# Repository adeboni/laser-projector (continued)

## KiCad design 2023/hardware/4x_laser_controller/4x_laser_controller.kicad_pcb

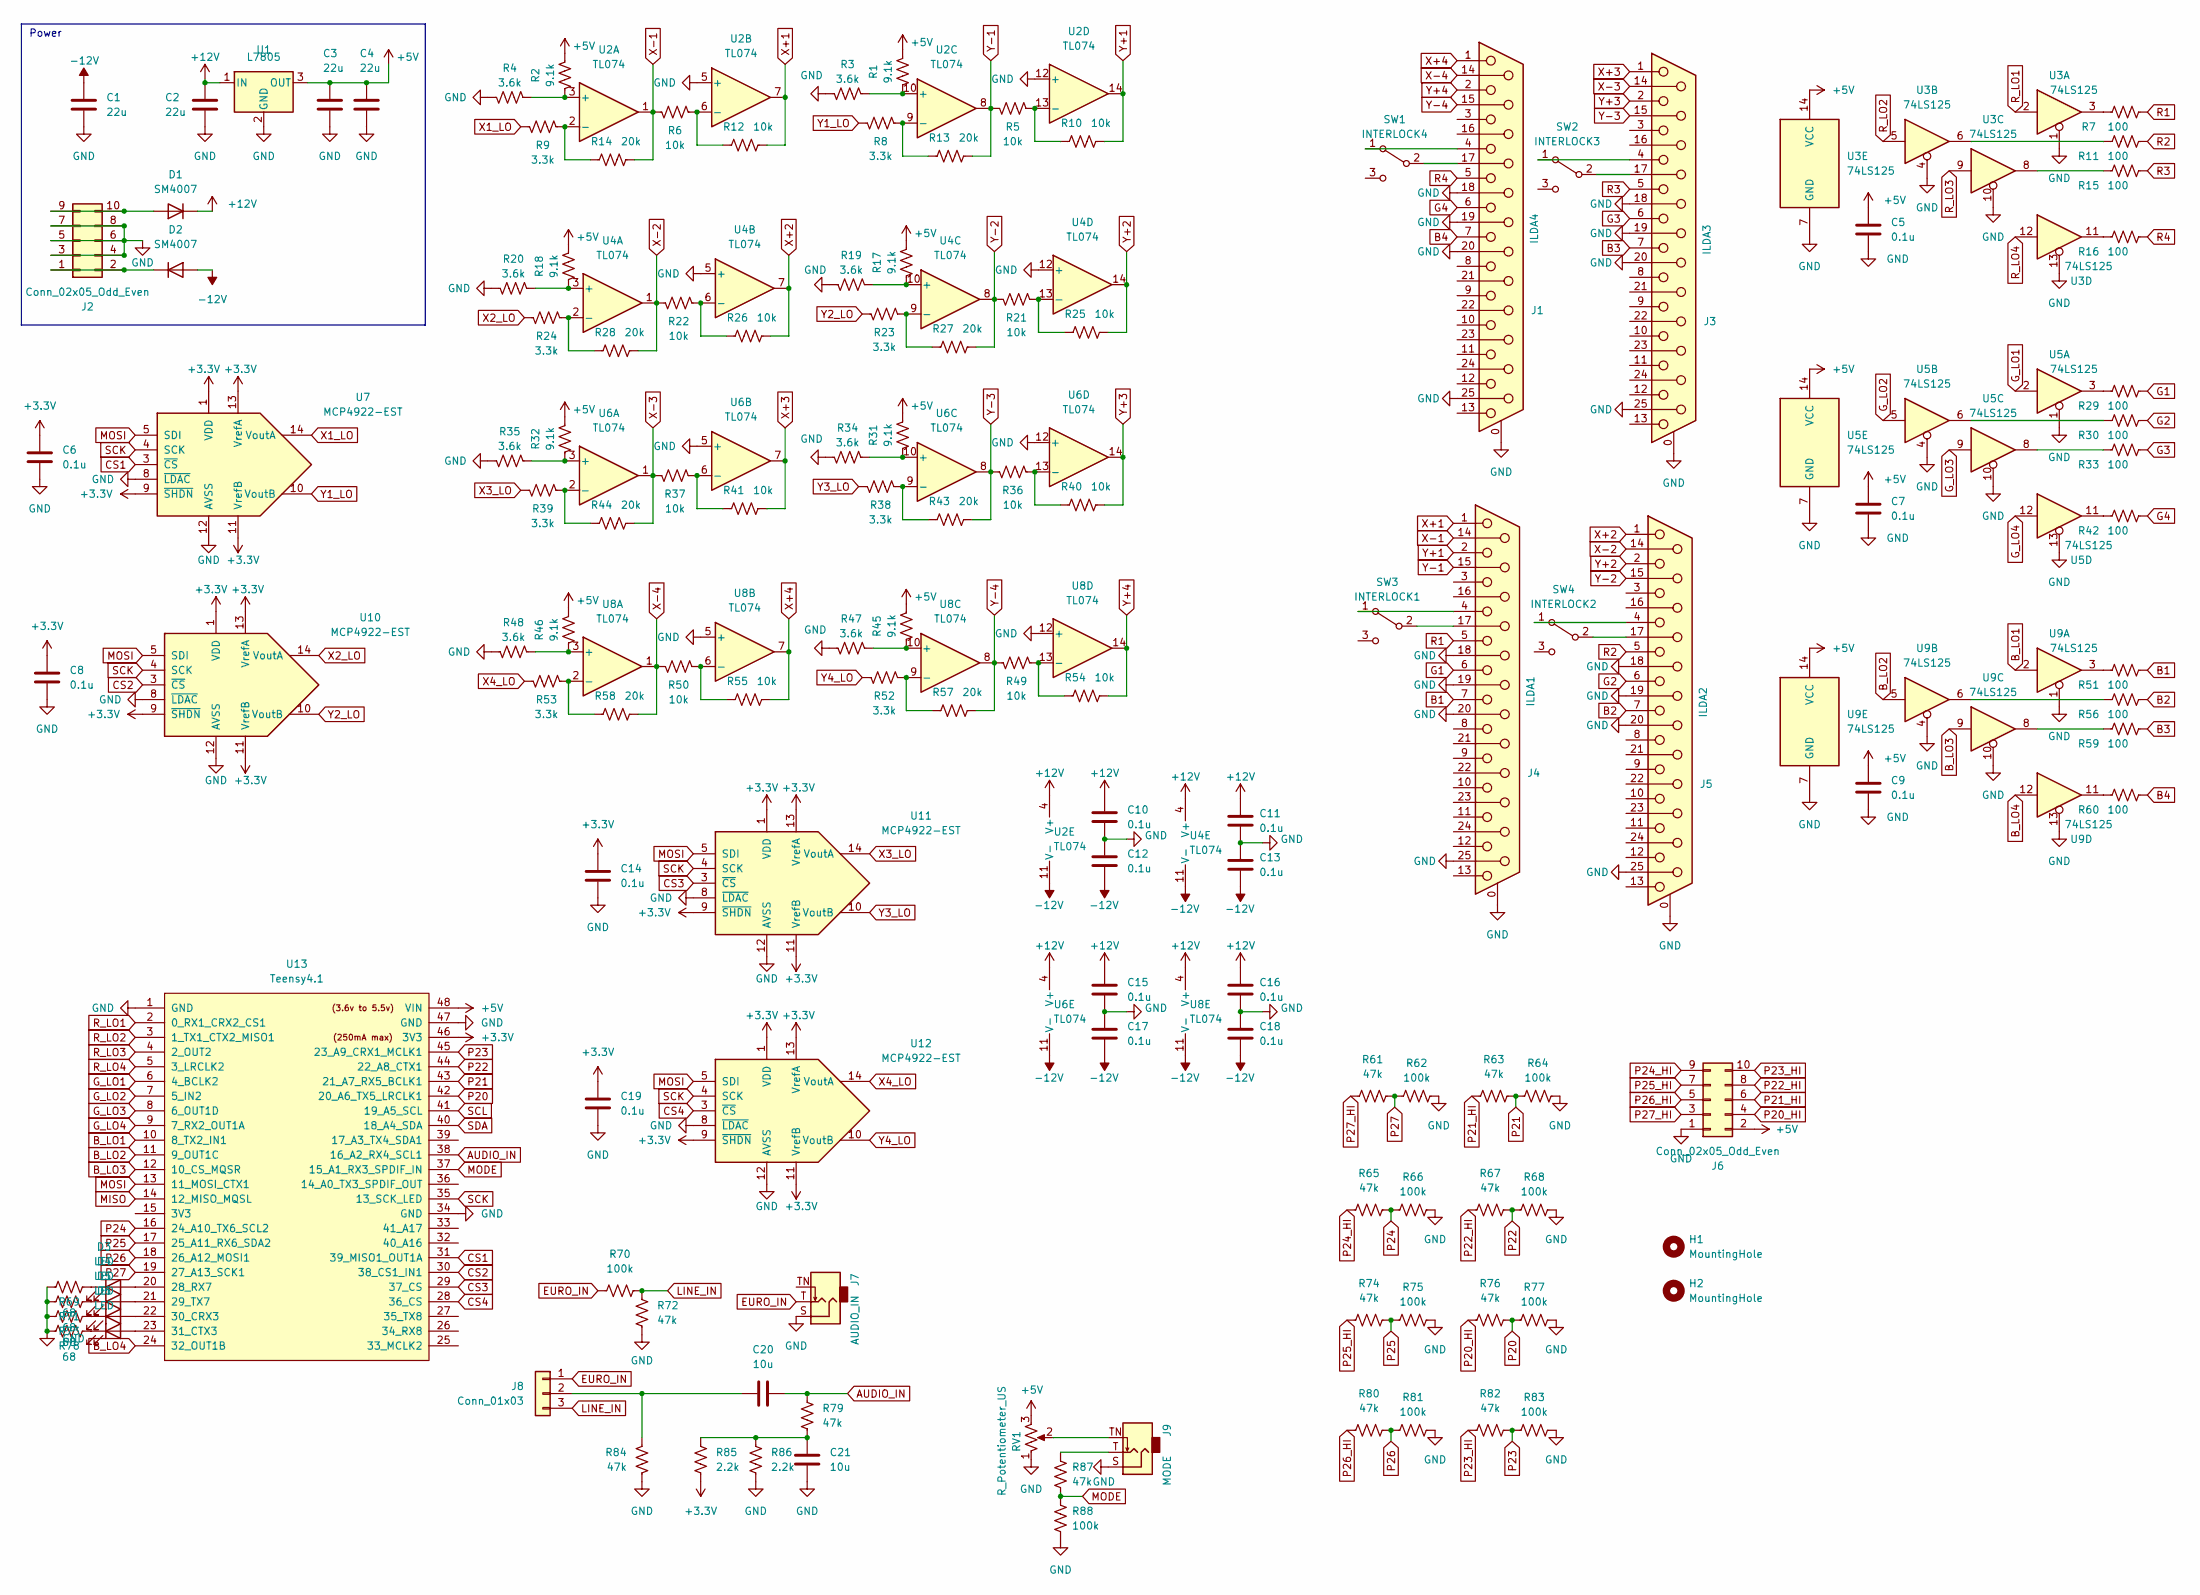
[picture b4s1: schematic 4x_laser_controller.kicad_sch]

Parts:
C1, C2, C3, C4: 22u; C_0805_2012Metric
C5, C6, C7, C8, C9, C10, C11, C12, C13, C14, C15, C16, C17, C18, C19: 0.1u; C_0603_1608Metric
C20, C21: 10u; C_0603_1608Metric
D1, D2: SM4007; D_SOD-123
D3, D4, D5, D6: LED; LED_D3.0mm
H1, H2: MountingHole; MountingHole_2.2mm_M2
J1: ILDA4; DSUB-25_Female_Vertical_P2.77x2.84mm_MountingHoles
J2, J6: Conn_02x05_Odd_Even; IDC-Header_2x05_P2.54mm_Vertical
J3: ILDA3; DSUB-25_Female_Vertical_P2.77x2.84mm_MountingHoles
J4: ILDA1; DSUB-25_Female_Vertical_P2.77x2.84mm_MountingHoles
J5: ILDA2; DSUB-25_Female_Vertical_P2.77x2.84mm_MountingHoles
J7: AUDIO_IN; Jack_3.5mm_QingPu_WQP-PJ398SM_Vertical_CircularHoles
J8: Conn_01x03; PinHeader_1x03_P2.54mm_Vertical
J9: MODE; Jack_3.5mm_QingPu_WQP-PJ398SM_Vertical_CircularHoles
R1, R2, R17, R18, R31, R32, R45, R46: 9.1k; R_0603_1608Metric
R3, R4, R19, R20, R34, R35, R47, R48: 3.6k; R_0603_1608Metric
R5, R6, R10, R12, R21, R22, R25, R26, R36, R37, R40, R41, R49, R50, R54, R55: 10k; R_0603_1608Metric
R7, R11, R15, R16, R29, R30, R33, R42, R51, R56, R59, R60: 100; R_0603_1608Metric
R8, R9, R23, R24, R38, R39, R52, R53: 3.3k; R_0603_1608Metric
R13, R14, R27, R28, R43, R44, R57, R58: 20k; R_0603_1608Metric
R61, R63, R65, R67, R72, R74, R76, R79, R80, R82, R84, R87: 47k; R_0603_1608Metric
R62, R64, R66, R68, R70, R75, R77, R81, R83, R88: 100k; R_0603_1608Metric
R69, R71, R73, R78: 68; R_0603_1608Metric
R85, R86: 2.2k; R_0603_1608Metric
RV1: R_Potentiometer_US; Potentiometer_Alpha_RD901F-40-00D_Single_Vertical
SW1: INTERLOCK4; Switch_Toggle_SPDT_Mini_SolderLug
SW2: INTERLOCK3; Switch_Toggle_SPDT_Mini_SolderLug
SW3: INTERLOCK1; Switch_Toggle_SPDT_Mini_SolderLug
SW4: INTERLOCK2; Switch_Toggle_SPDT_Mini_SolderLug
U1: L7805; TO-252-2
U2, U4, U6, U8: TL074; SOIC-14_3.9x8.7mm_P1.27mm
U3, U5, U9: 74LS125; SOIC-14_3.9x8.7mm_P1.27mm
U7, U10, U11, U12: MCP4922-EST; TSSOP-14_4.4x5mm_P0.65mm
U13: Teensy4.1; Teensy41

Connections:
+3V3: C6.2, C8.2, C14.2, C19.2, R85.1, U7.1 (VDD), U7.9 (~SHDN), U7.11 (VrefB), U7.13 (VrefA), U10.1 (VDD), U10.9 (~SHDN), U10.11 (VrefB), U10.13 (VrefA), U11.1 (VDD), U11.9 (~SHDN), U11.11 (VrefB), U11.13 (VrefA), U12.1 (VDD), U12.9 (~SHDN), U12.11 (VrefB), U12.13 (VrefA), U13.46 (3V3)
+5V: C3.1, C4.1, C5.1, C7.1, C9.1, J6.2, R1.2, R2.2, R17.2, R18.2, R31.2, R32.2, R45.2, R46.2, RV1.3, U1.3 (OUT), U3.14 (VCC), U5.14 (VCC), U9.14 (VCC), U13.48 (VIN)
+12V: C2.1, C10.1, C11.1, C15.1, C16.1, D1.1 (K), U1.1 (IN), U2.4 (V+), U4.4 (V+), U6.4 (V+), U8.4 (V+)
-12V: C1.1, C12.2, C13.2, C17.2, C18.2, D2.2 (A), U2.11 (V-), U4.11 (V-), U6.11 (V-), U8.11 (V-)
AUDIO_IN: C20.2, R79.2, U13.38 (16_A2_RX4_SCL1)
B1: J4.7, R51.2
B2: J5.7, R56.2
B3: J3.7, R59.2
B4: J1.7, R60.2
B_LO1: U9.2, U13.10 (8_TX2_IN1)
B_LO2: U9.5, U13.11 (9_OUT1C)
B_LO3: U9.9, U13.12 (10_CS_MQSR)
B_LO4: U9.12, U13.24 (32_OUT1B)
CS1: U7.3 (~CS), U13.31 (39_MISO1_OUT1A)
CS2: U10.3 (~CS), U13.30 (38_CS1_IN1)
CS3: U11.3 (~CS), U13.29 (37_CS)
CS4: U12.3 (~CS), U13.28 (36_CS)
EURO_IN: J7.T, J8.1, R70.1
G1: J4.6, R29.2
G2: J5.6, R30.2
G3: J3.6, R33.2
G4: J1.6, R42.2
GND: C1.2, C2.2, C3.2, C4.2, C5.2, C6.1, C7.2, C8.1, C9.2, C10.2, C11.2, C12.1, C13.1, C14.1, C15.2, C16.2, C17.1, C18.1, C19.1, C21.1, J1.0 (PAD), J1.18, J1.19, J1.20, J1.25, J2.3, J2.4, J2.5, J2.6, J2.7, J2.8, J3.0 (PAD), J3.18, J3.19, J3.20, J3.25, J4.0 (PAD), J4.18, J4.19, J4.20, J4.25, J5.0 (PAD), J5.18, J5.19, J5.20, J5.25, J6.1, J7.S, J9.S, R3.1, R4.1, R19.1, R20.1, R34.1, R35.1, R47.1, R48.1, R62.1, R64.1, R66.1, R68.1, R69.1, R71.1, R72.1, R73.1, R75.1, R77.1, R78.1, R81.1, R83.1, R84.1, R86.1, R88.2, RV1.1, U1.2 (GND), U2.5 (+), U2.12 (+), U3.1, U3.4, U3.7 (GND), U3.10, U3.13, U4.5 (+), U4.12 (+), U5.1, U5.4, U5.7 (GND), U5.10, U5.13, U6.5 (+), U6.12 (+), U7.8 (~LDAC), U7.12 (AVSS), U8.5 (+), U8.12 (+), U9.1, U9.4, U9.7 (GND), U9.10, U9.13, U10.8 (~LDAC), U10.12 (AVSS), U11.8 (~LDAC), U11.12 (AVSS), U12.8 (~LDAC), U12.12 (AVSS), U13.1 (GND), U13.34 (GND), U13.47 (GND)
G_LO1: U5.2, U13.6 (4_BCLK2)
G_LO2: U5.5, U13.7 (5_IN2)
G_LO3: U5.9, U13.8 (6_OUT1D)
G_LO4: U5.12, U13.9 (7_RX2_OUT1A)
LINE_IN: J8.3, R70.2, R72.2
MISO: U13.14 (12_MISO_MQSL)
MODE: R87.1, R88.1, U13.37 (15_A1_RX3_SPDIF_IN)
MOSI: U7.5 (SDI), U10.5 (SDI), U11.5 (SDI), U12.5 (SDI), U13.13 (11_MOSI_CTX1)
unnamed: C20.1, J8.2, R84.2
unnamed: C21.2, R79.1, R85.2, R86.2
unnamed: D1.2 (A), J2.9, J2.10
unnamed: D2.1 (K), J2.1, J2.2
unnamed: D3.1 (K), R69.2
unnamed: D3.2 (A), U13.20 (28_RX7)
unnamed: D4.1 (K), R71.2
unnamed: D4.2 (A), U13.21 (29_TX7)
unnamed: D5.1 (K), R73.2
unnamed: D5.2 (A), U13.22 (30_CRX3)
unnamed: D6.1 (K), R78.2
unnamed: D6.2 (A), U13.23 (31_CTX3)
unnamed: J1.4, SW1.1 (A)
unnamed: J1.17, SW1.2 (B)
unnamed: J3.4, SW2.1 (A)
unnamed: J3.17, SW2.2 (B)
unnamed: J4.4, SW3.1 (A)
unnamed: J4.17, SW3.2 (B)
unnamed: J5.4, SW4.1 (A)
unnamed: J5.17, SW4.2 (B)
unnamed: J9.T, R87.2
unnamed: J9.TN, RV1.2
unnamed: R1.1, R3.2, U2.10 (+)
unnamed: R2.1, R4.2, U2.3 (+)
unnamed: R7.1, U3.3
unnamed: R5.2, R10.1, U2.13 (-)
unnamed: R11.1, U3.6
unnamed: R6.2, R12.1, U2.6 (-)
unnamed: R8.2, R13.1, U2.9 (-)
unnamed: R9.2, R14.1, U2.2 (-)
unnamed: R15.1, U3.8
unnamed: R16.1, U3.11
unnamed: R17.1, R19.2, U4.10 (+)
unnamed: R18.1, R20.2, U4.3 (+)
unnamed: R21.2, R25.1, U4.13 (-)
unnamed: R22.2, R26.1, U4.6 (-)
unnamed: R23.2, R27.1, U4.9 (-)
unnamed: R24.2, R28.1, U4.2 (-)
unnamed: R29.1, U5.3
unnamed: R30.1, U5.6
unnamed: R31.1, R34.2, U6.10 (+)
unnamed: R32.1, R35.2, U6.3 (+)
unnamed: R33.1, U5.8
unnamed: R36.2, R40.1, U6.13 (-)
unnamed: R37.2, R41.1, U6.6 (-)
unnamed: R38.2, R43.1, U6.9 (-)
unnamed: R39.2, R44.1, U6.2 (-)
unnamed: R42.1, U5.11
unnamed: R45.1, R47.2, U8.10 (+)
unnamed: R46.1, R48.2, U8.3 (+)
unnamed: R49.2, R54.1, U8.13 (-)
unnamed: R50.2, R55.1, U8.6 (-)
unnamed: R51.1, U9.3
unnamed: R52.2, R57.1, U8.9 (-)
unnamed: R53.2, R58.1, U8.2 (-)
unnamed: R56.1, U9.6
unnamed: R59.1, U9.8
unnamed: R60.1, U9.11
P20: R76.2, R77.2, U13.42 (20_A6_TX5_LRCLK1)
P20_HI: J6.4, R76.1
P21: R63.2, R64.2, U13.43 (21_A7_RX5_BCLK1)
P21_HI: J6.6, R63.1
P22: R67.2, R68.2, U13.44 (22_A8_CTX1)
P22_HI: J6.8, R67.1
P23: R82.2, R83.2, U13.45 (23_A9_CRX1_MCLK1)
P23_HI: J6.10, R82.1
P24: R65.2, R66.2, U13.16 (24_A10_TX6_SCL2)
P24_HI: J6.9, R65.1
P25: R74.2, R75.2, U13.17 (25_A11_RX6_SDA2)
P25_HI: J6.7, R74.1
P26: R80.2, R81.2, U13.18 (26_A12_MOSI1)
P26_HI: J6.5, R80.1
P27: R61.2, R62.2, U13.19 (27_A13_SCK1)
P27_HI: J6.3, R61.1
R1: J4.5, R7.2
R2: J5.5, R11.2
R3: J3.5, R15.2
R4: J1.5, R16.2
R_LO1: U3.2, U13.2 (0_RX1_CRX2_CS1)
R_LO2: U3.5, U13.3 (1_TX1_CTX2_MISO1)
R_LO3: U3.9, U13.4 (2_OUT2)
R_LO4: U3.12, U13.5 (3_LRCLK2)
SCK: U7.4 (SCK), U10.4 (SCK), U11.4 (SCK), U12.4 (SCK), U13.35 (13_SCK_LED)
SCL: U13.41 (19_A5_SCL)
SDA: U13.40 (18_A4_SDA)
X1_LO: R9.1, U7.14 (VoutA)
X2_LO: R24.1, U10.14 (VoutA)
X3_LO: R39.1, U11.14 (VoutA)
X4_LO: R53.1, U12.14 (VoutA)
X+1: J4.1, R12.2, U2.7
X+2: J5.1, R26.2, U4.7
X+3: J3.1, R41.2, U6.7
X+4: J1.1, R55.2, U8.7
X-1: J4.14, R6.1, R14.2, U2.1
X-2: J5.14, R22.1, R28.2, U4.1
X-3: J3.14, R37.1, R44.2, U6.1
X-4: J1.14, R50.1, R58.2, U8.1
Y1_LO: R8.1, U7.10 (VoutB)
Y2_LO: R23.1, U10.10 (VoutB)
Y3_LO: R38.1, U11.10 (VoutB)
Y4_LO: R52.1, U12.10 (VoutB)
Y+1: J4.2, R10.2, U2.14
Y+2: J5.2, R25.2, U4.14
Y+3: J3.2, R40.2, U6.14
Y+4: J1.2, R54.2, U8.14
Y-1: J4.15, R5.1, R13.2, U2.8
Y-2: J5.15, R21.1, R27.2, U4.8
Y-3: J3.15, R36.1, R43.2, U6.8
Y-4: J1.15, R49.1, R57.2, U8.8

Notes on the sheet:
Power

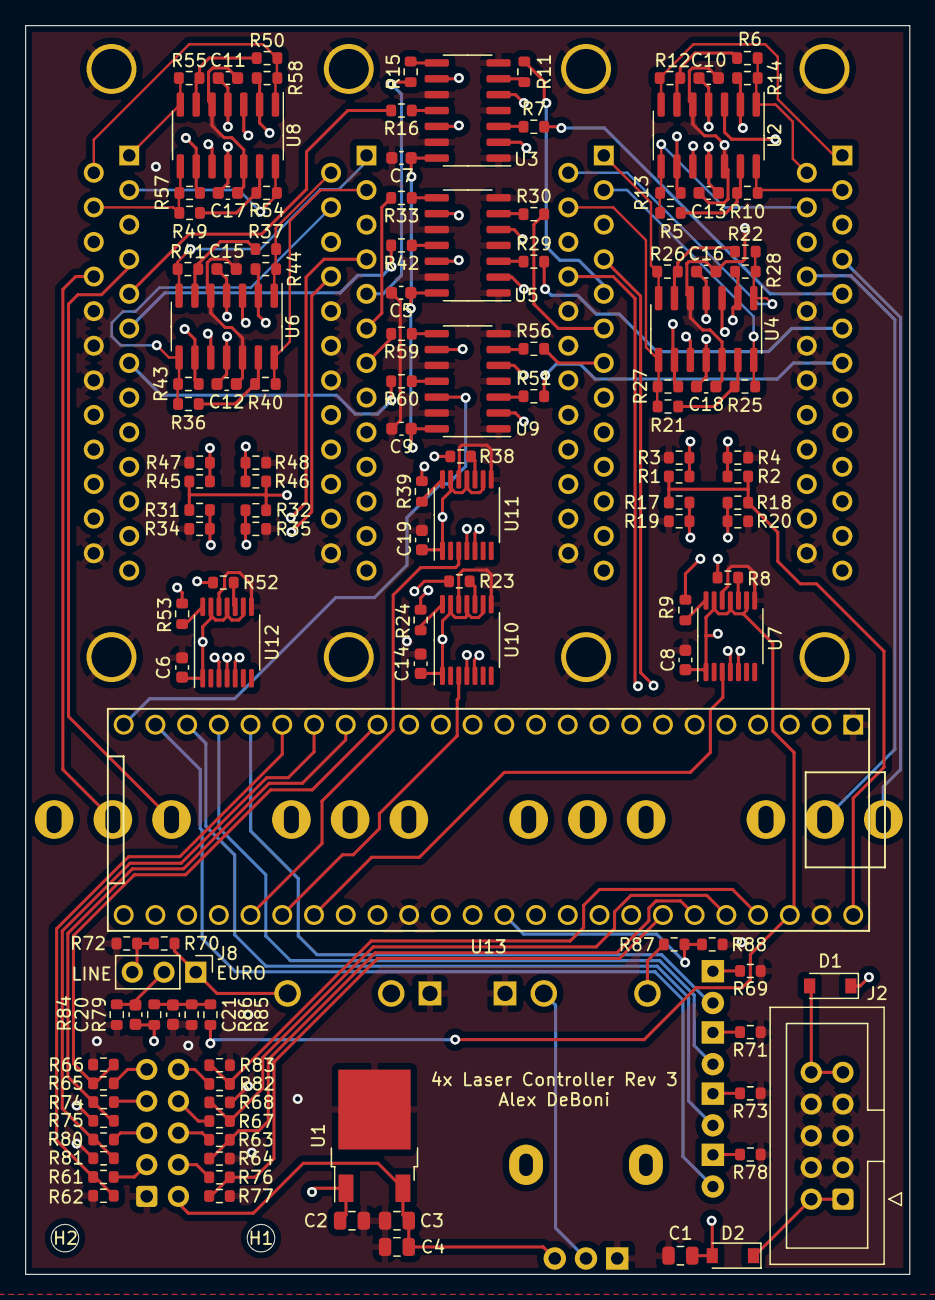
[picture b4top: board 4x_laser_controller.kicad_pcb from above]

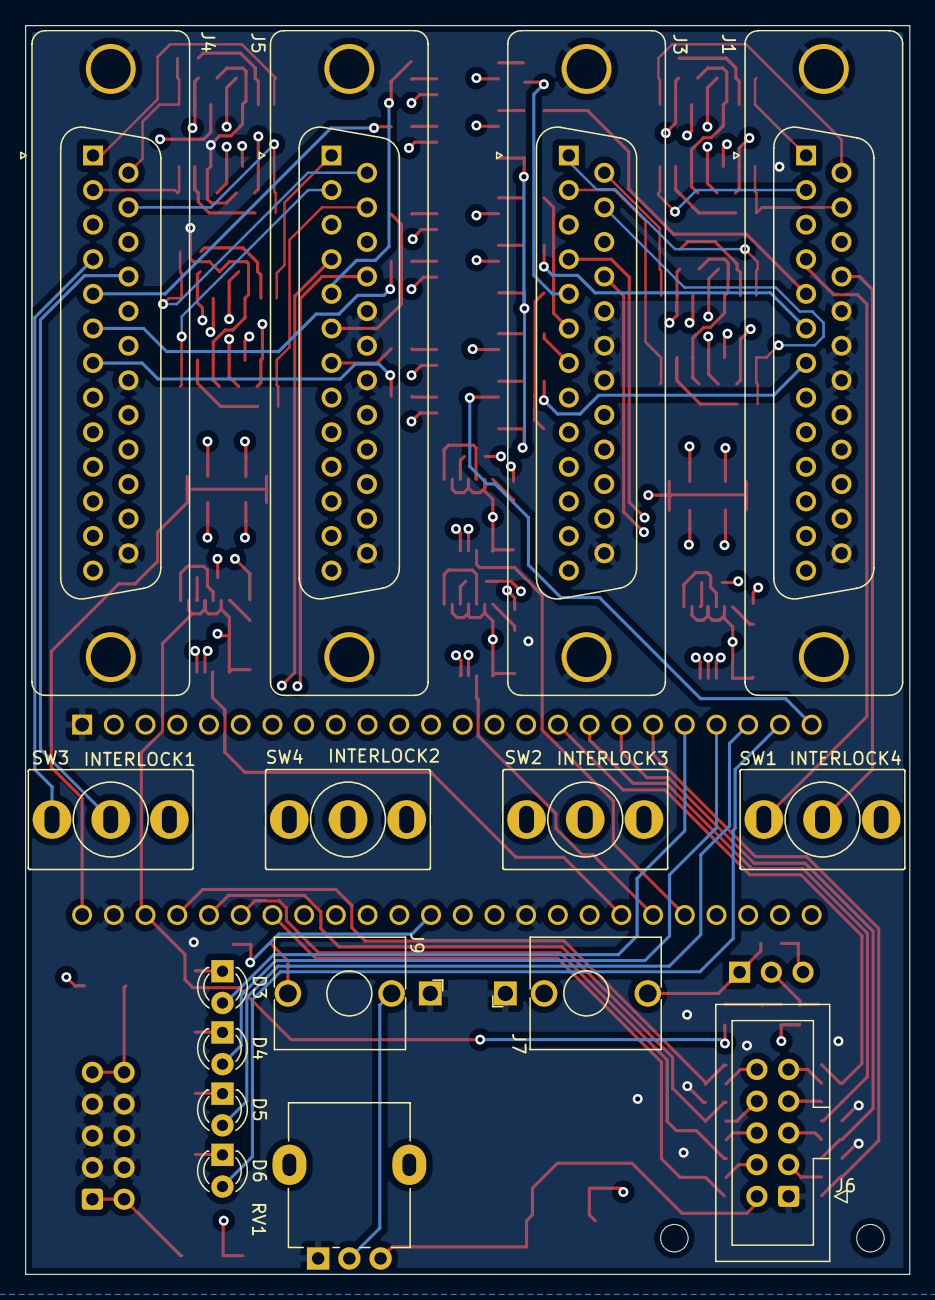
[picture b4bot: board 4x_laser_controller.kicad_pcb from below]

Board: 4 copper layers, 70.8 x 100.0 mm, 144 parts (16 on the bottom side), 137 nets.

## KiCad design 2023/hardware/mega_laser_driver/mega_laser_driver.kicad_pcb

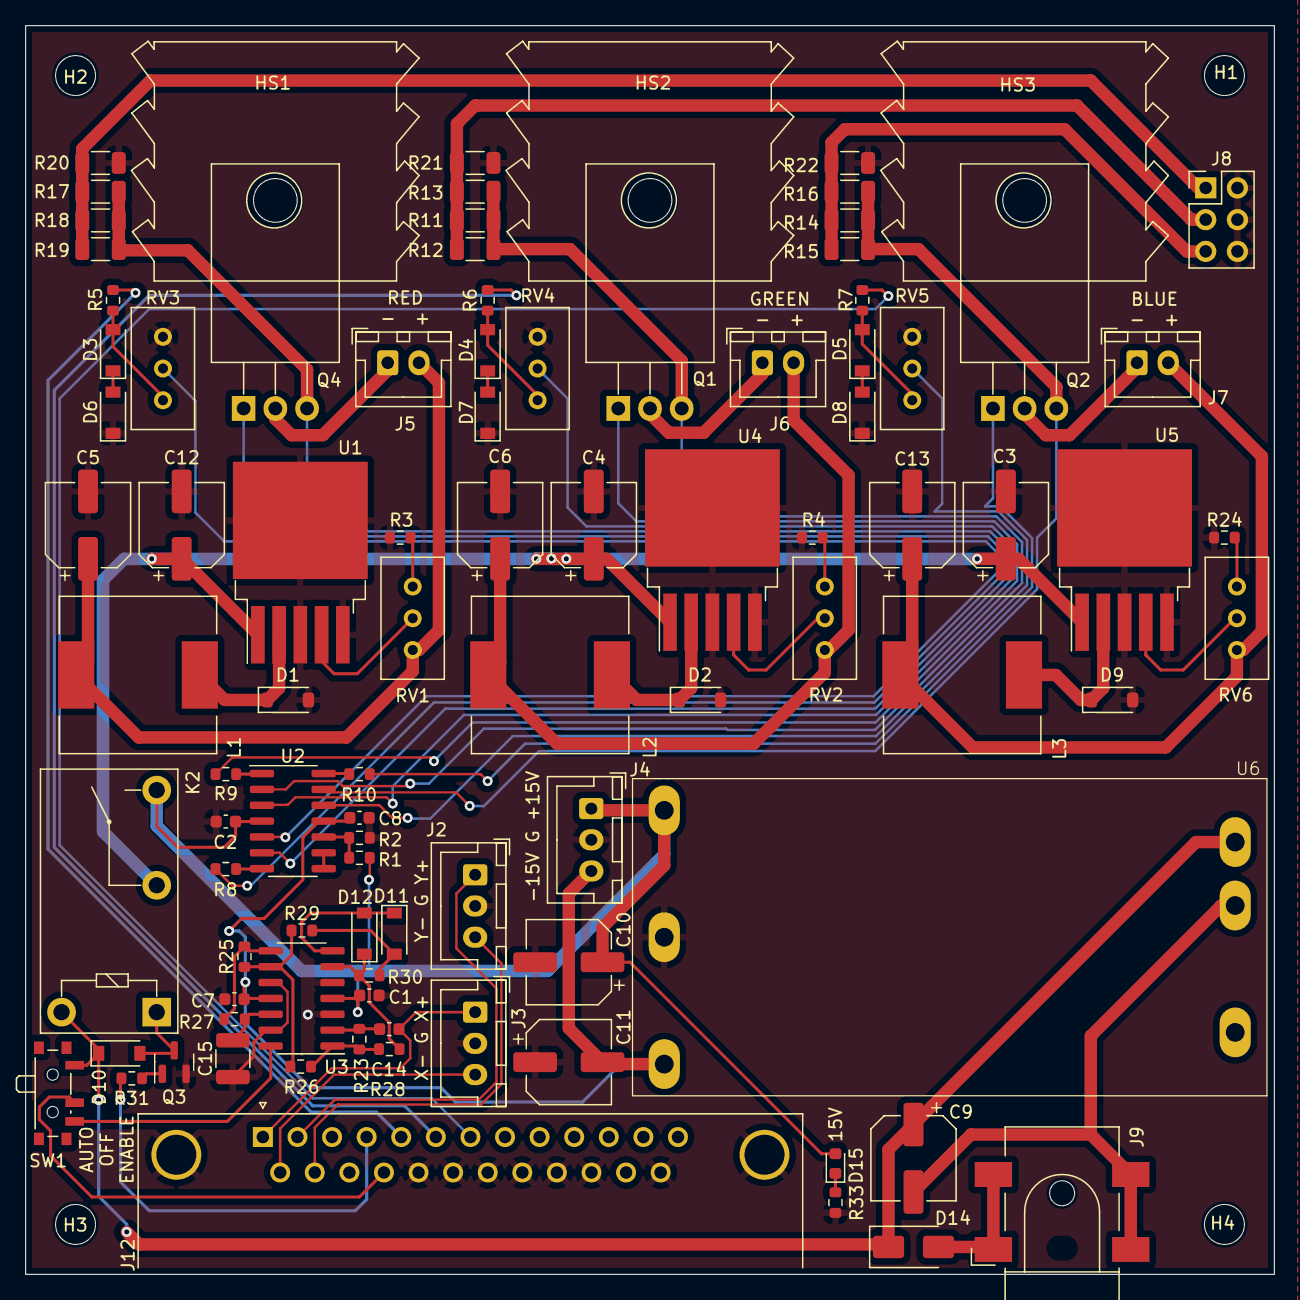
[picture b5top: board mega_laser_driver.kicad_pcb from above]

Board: 2 copper layers, 100.0 x 100.0 mm, 98 parts (0 on the bottom side), 66 nets.

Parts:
C1, C2, C7, C8: 100n; C_0603_1608Metric
C3, C4, C5, C6, C9, C10, C11, C12, C13: 220u; CP_Elec_6.3x7.7
C14: 2u; C_0603_1608Metric
C15: 47u; C_1210_3225Metric
D1, D2, D9: 1N5819WS; D_SOD-123
D3, D4, D5, D6, D7, D8, D10, D11, D12: 1N4148W; D_SOD-123
D14: SS54; D_SMA
D15: LED; LED_0603_1608Metric
H1, H2, H3, H4: MountingHole; MountingHole_3.2mm_M3
HS1, HS2, HS3: Heatsink; Heatsink_AAVID_TV5G_TO220_Horizontal
J2, J3, J4: Conn_01x03; JST_XH_B3B-XH-A_1x03_P2.50mm_Vertical
J5, J6, J7: Conn_01x02; JST_XH_B2B-XH-A_1x02_P2.50mm_Vertical
J8: Conn_02x03_Odd_Even; PinHeader_2x03_P2.54mm_Vertical
J9: Barrel_Jack_Switch; BarrelJack_CLIFF_FC681465S_SMT_Horizontal
J12: DB25_Plug_MountingHoles; DSUB-25_Male_Horizontal_P2.77x2.84mm_EdgePinOffset7.70mm_Ho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
K2: G5Q-1A-DC12; Relay_SPST_Omron-G5Q-1A
L1, L2, L3: 150uH; L_12x12mm_H8mm
Q1, Q2, Q4: TIP120; TO-220-3_Horizontal_TabDown
Q3: 2N7002; SOT-23
R1, R2: 10k; R_0603_1608Metric
R3, R4, R24: 1.2k; R_0603_1608Metric
R5, R6, R7: 33k; R_0603_1608Metric
R8, R9, R10, R31: 100; R_0603_1608Metric
R11, R12, R13, R14, R15, R16, R17, R18, R19, R20, R21, R22: 10R; R_1206_3216Metric
R23: 5k; R_0603_1608Metric
R25, R26, R27, R28, R30: 1k; R_0603_1608Metric
R29: 500; R_0603_1608Metric
R33: 680; R_0603_1608Metric
RV1, RV2, RV3, RV4, RV5, RV6: 10k; Potentiometer_Bourns_3296W_Vertical
SW1: SW_SPDT; SW_SPDT_PCM12
U1, U4, U5: LM2576S-ADJ; TO-263-5_TabPin3
U2, U3: LM324; SOIC-14_3.9x8.7mm_P1.27mm
U6: TEN20-2422WIN; PYBE30-Q24-D15

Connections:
+12V: C9.1, D10.1 (K), D14.1 (K), K2.5, SW1.1 (A), U6.1 (VIN+)
+15V: C1.1, C2.1, C10.1, D15.2 (A), J4.1, K2.3, R1.2, U2.4 (V+), U3.4 (V+), U6.6 (VOUT+)
-15V: C7.1, C8.1, C11.2, J4.3, U2.11 (V-), U3.11 (V-), U6.4 (VOUT-)
BLUE: J12.7, R7.2
GND: C1.2, C2.2, C3.2, C4.2, C5.2, C6.2, C7.2, C8.2, C10.2, C11.1, C12.2, C13.2, C15.1, D1.2 (A), D2.2 (A), D6.1 (K), D7.1 (K), D8.1 (K), D9.2 (A), J2.2, J3.2, J4.2, J8.2, J8.4, J8.6, J12.0 (PAD), J12.18, J12.19, J12.20, J12.21, J12.22, J12.23, J12.25, Q3.2 (S), R2.1, R3.1, R4.1, R20.2, R21.2, R22.2, R24.1, R33.2, RV3.3, RV4.3, RV5.3, U1.3 (GND), U1.5 (~ON/OFF), U3.3 (+), U3.5 (+), U3.10 (+), U3.13 (-), U4.3 (GND), U4.5 (~ON/OFF), U5.3 (GND), U5.5 (~ON/OFF), U6.5 (CM)
GREEN: J12.6, R6.2
INTERLOCK1: J12.4, R31.1
INTERLOCK2: J12.17, SW1.2 (B)
MOTOR_ON: SW1.3 (C), U3.14
unnamed: D1.1 (K), L1.1, U1.2 (OUT)
unnamed: D2.1 (K), L2.1, U4.2 (OUT)
unnamed: D3.2 (A), R5.1, RV3.1
unnamed: D3.1 (K), D6.2 (A)
unnamed: D4.2 (A), R6.1, RV4.1
unnamed: D4.1 (K), D7.2 (A)
unnamed: D5.2 (A), R7.1, RV5.1
unnamed: D5.1 (K), D8.2 (A)
unnamed: D9.1 (K), L3.1, U5.2 (OUT)
unnamed: D10.2 (A), K2.1, Q3.3 (D)
unnamed: D11.2 (A), R29.1, R30.1
unnamed: D11.1 (K), D12.2 (A), U3.7
unnamed: D12.1 (K), R28.2, R30.2, U3.6 (-)
unnamed: D14.2 (A), J9.1
unnamed: D15.1 (K), R33.1
unnamed: J5.1, Q4.2 (C)
unnamed: J6.1, Q1.2 (C)
unnamed: J7.1, Q2.2 (C)
unnamed: J8.1, R17.2, R18.2, R19.2, R20.1
unnamed: J8.3, R11.2, R12.2, R13.2, R21.1
unnamed: J8.5, R14.2, R15.2, R16.2, R22.1
unnamed: Q1.1 (B), R9.2
unnamed: Q1.3 (E), R11.1, R12.1, R13.1, U2.2 (-)
unnamed: Q2.1 (B), R10.2
unnamed: Q2.3 (E), R14.1, R15.1, R16.1, U2.13 (-)
unnamed: Q3.1 (G), R31.2
unnamed: Q4.1 (B), R8.2
unnamed: Q4.3 (E), R17.1, R18.1, R19.1, U2.6 (-)
unnamed: R3.2, RV1.3
unnamed: R4.2, RV2.3
unnamed: R8.1, U2.7
unnamed: R9.1, U2.1
unnamed: R10.1, U2.14
unnamed: R23.2, R26.1, R28.1, U3.1
unnamed: R24.2, RV6.3
unnamed: R25.2, R27.1, U3.8
unnamed: RV1.2, U1.4 (FB)
unnamed: RV4.2, U2.3 (+)
unnamed: RV3.2, U2.5 (+)
unnamed: R1.1, R2.2, U2.10 (+)
unnamed: U2.8, U2.9 (-)
unnamed: RV5.2, U2.12 (+)
unnamed: C14.2, R23.1, U3.2 (-)
unnamed: R25.1, R26.2, R29.2, U3.9 (-)
unnamed: C15.2, R27.2, U3.12 (+)
unnamed: RV2.2, U4.4 (FB)
unnamed: RV6.2, U5.4 (FB)
unnamed: C9.2, J9.2, J9.3, U6.2 (VIN-)
RED: J12.5, R5.2
V1: C5.1, J5.2, L1.2, RV1.1
V2: C6.1, J6.2, L2.2, RV2.1
V3: C13.1, J7.2, L3.2, RV6.1
VCC: C3.1, C4.1, C12.1, K2.2, U1.1 (VIN), U4.1 (VIN), U5.1 (VIN)
X+: C14.1, J3.1, J12.1
X-: J3.3, J12.14
Y+: J2.1, J12.2
Y-: J2.3, J12.15

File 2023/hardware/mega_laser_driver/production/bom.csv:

Designator,Footprint,Quantity,Value,LCSC Part #
"C1, C2, C7, C8",603,4,100n,C14663
"C10, C11, C12, C13, C3, C4, C5, C6, C9",CP_Elec_6.3x7.7,9,220u,C340768
C14,603,1,2u,C23630
C15,1210,1,47u,C90142
"D1, D2, D9",D_SOD-123,3,1N5819WS,C8598
"D10, D11, D12, D3, D4, D5, D6, D7, D8",D_SOD-123,9,1N4148W,C81598
"D13, D15",603,2,LED,C2286
D14,D_SMA,1,SS54,C22452
J9,BarrelJack_CLIFF_FC681465S_SMT_Horizontal,1,Barrel_Jack_Switch,C431534
"L1, L2, L3",L_12x12mm_H8mm,3,150uH,C339958
Q3,SOT-23,1,2N7002,C8545
"R1, R2",603,2,10k,C25804
"R10, R31, R8, R9",603,4,100,C22775
"R11, R12, R13, R14, R15, R16, R17, R18, R19, R20, R21, R22",1206,12,10R,C17903
R23,603,1,5k,C23186
"R24, R3, R4",603,3,1.2k,C22765
"R25, R26, R27, R28, R30",603,5,1k,C21190
R29,603,1,500,C23193
R32,603,1,560,C23204
R33,603,1,680,C23228
"R5, R6, R7",603,3,33k,C4216
SW1,SW_SPDT_PCM12,1,SW_SPDT,C319019
"U1, U4, U5",TO-263-5_TabPin3,3,LM2576S-ADJ,C347415
"U2, U3",SOIC-14_3.9x8.7mm_P1.27mm,2,LM324,C71035

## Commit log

2022-12-08 initial working prototype
2022-12-08 Added hardware and re-organized files
2022-12-08 Create LICENSE
2022-12-08 Added more PCBs
2022-12-08 Re-organized source code
2022-12-08 Added code to draw the outline of a mesh with sorted edges
2022-12-22 Improved laser driver design
    The laser driver now allows you to switch between two different brightnesses with an external switch
2022-12-29 Updated laser driver fab files
2023-01-01 Added DB25 right angle adapter
2023-01-10 Updated laser driver silkscreen
2023-01-23 Added extra mode for color testing
2023-01-24 Added laser PWM control
2023-01-26 Optimized mesh processing
2023-01-26 Added text and object tests
2023-01-29 Added new demos
2023-02-03 Made some performance optimizations
2023-04-19 Added calibration routines and changed longs to ints and floats
2023-06-02 Added perspective adjustment
2023-06-05 Bug fixes and speed improvements
2023-06-05 Enabled perspective warping
2023-06-13 Implemented a mostly-working frame buffer
2023-06-14 Got the frame buffer working
2023-06-14 Improved mesh memory usage
2023-07-27 Added new hardware
2023-08-14 Added display-adapter support
2023-08-15 Added final laser modes
2023-08-20 Added equations and improved calibration mode
2023-08-21 Updated animations
2023-08-21 Fixed vectors
2023-11-15 Minor pcb edits
2023-11-15 Updated to latest versions
2023-11-15 Added initial firmware
2023-11-15 Removed duplicate files
2023-11-15 Removed sACN streaming from laser
2023-11-16 Added http requests to laser
2023-11-16 Added more flask tests
2023-11-16 Got the flask server working
2023-11-16 Minor refactoring
2023-11-17 Minor fixes
2023-11-17 Minor code cleanup
2023-11-18 More testing
2023-11-18 Got client server code mostly working
2023-11-18 Added a timeout to cut laser power
2023-11-21 Added sACN support for the UI board
2023-11-22 Removed sACN files
2023-11-22 Added sACN client simulator
2023-11-22 Minor code refactoring
2023-11-30 Minor updates
2023-12-19 Updated sACN examples
2024-01-03 Added booklet generator
2024-01-03 Added WSGI server
2024-01-03 Changed WSGI server to waitress
2024-01-10 Switched ui from tkinter to pygame
2024-01-10 Simplified some server code
2024-01-11 Added INA219 script
2024-01-11 Changed port to 8080
2024-01-22 Added code to update LCDs
2024-01-23 Minor updates to sacn and the INA219 script
2024-01-29 Added robbie animation handler
2024-01-29 Added more animations
2024-01-29 Some minor bug fixes
2024-01-30 Updated button light handler
2024-02-01 Added time delay to sacn start
2024-02-01 Added decorators
2024-02-06 Updated laser simulator
2024-02-07 Added laser object graphics
2024-02-08 Added more laser graphics examples
2024-02-12 Added spirograph generator
2024-02-13 Updated queue sizes
2024-02-13 Got laser hardware working with waitress
2024-02-13 Added automatic IP address selection
2024-02-13 Added object visualizer
2024-02-13 Fixed interpolation bug
2024-02-14 Updated queue behavior
2024-02-20 Added bouncing ball generator
2024-02-20 Added some comments
2024-03-01 Added wand class
2024-03-11 Switched from TCP to UDP
2024-03-11 Update UDP behavior
2024-03-11 Optimized laser server
2024-03-11 Updated packet timing
2024-03-12 Updated mode names
2024-03-29 Added audio visualization
2024-03-29 Import cleanup
2024-04-01 Misc updates
2024-04-02 Fixed wand rotation calculation
2024-04-02 Added audio envelope function
2024-04-03 Added more laser graphics
2024-04-05 Code cleanup
2024-04-08 Added wand drawing
2024-04-09 Added functionality to pause music for certain modes
2024-04-09 Fixed time delay decorator bug
2024-04-09 Allow wands to update without window focus
2024-04-10 Fixed graphic centering bug
2024-04-15 Allowed wands to play effect samples
2024-04-16 Updated equation animation
2024-04-17 Added wand simulator
2024-04-18 Updated synthesizer
2024-04-19 Expanded wand support
2024-04-22 Added wand visualizer
2024-04-23 Wand updates
2024-04-24 Updated wand visualizer
2024-04-24 Wand calibration updates
2024-04-24 Removed wand visualization from sierpinski
2024-04-24 Updated wand calibration
2024-04-25 Added automatic wand scanning
2024-04-25 Updated wand rotation math
2024-04-25 Added quaternion-based wand simulator
2024-04-26 Fix some wand calculations
2024-04-26 Updated visualizer
2024-04-30 Refactored synthesizer code
2024-04-30 Updated synthdef
2024-05-01 Added raspi_files folder
2024-05-01 Added robbie sound effects
2024-05-02 Added more raspi files
2024-05-03 Prepared code for new wand firmware
2024-05-07 Replaced bleak with simpleble
2024-05-07 Removed update position call from wands
2024-05-07 Made synth updates threaded
2024-05-08 Converted simpleble back to bleak
2024-05-10 Added code to keep focus on main app and retry synth server connect
2024-05-10 Updated refocus code
2024-06-10 Added new drum mode
2024-06-10 Added more effects
2024-06-25 Added notes
2024-06-28 Added wand button short/long press
2024-06-28 Added firework effect on wand button press
2024-06-28 Updated button press logic
2024-06-29 Minor bug fixes
2024-07-01 Updates from latest demo
2024-07-09 Updated equation vectors
2024-07-22 Updated booklet generator
2024-07-28 Added song logging
2024-08-01 Updated audio vis scaling
2024-09-30 Updates from the field
2024-10-08 Added TCP wand support
2024-10-09 Switched to UDP
2024-10-09 Wand quaternion experiments
2024-10-10 Wand quaternion optimizations
2024-10-15 Updated calibration procedure
2024-10-30 Added 2025 firmware
2024-10-30 Removed 2025 firmware
2024-11-02 Bug fixes
